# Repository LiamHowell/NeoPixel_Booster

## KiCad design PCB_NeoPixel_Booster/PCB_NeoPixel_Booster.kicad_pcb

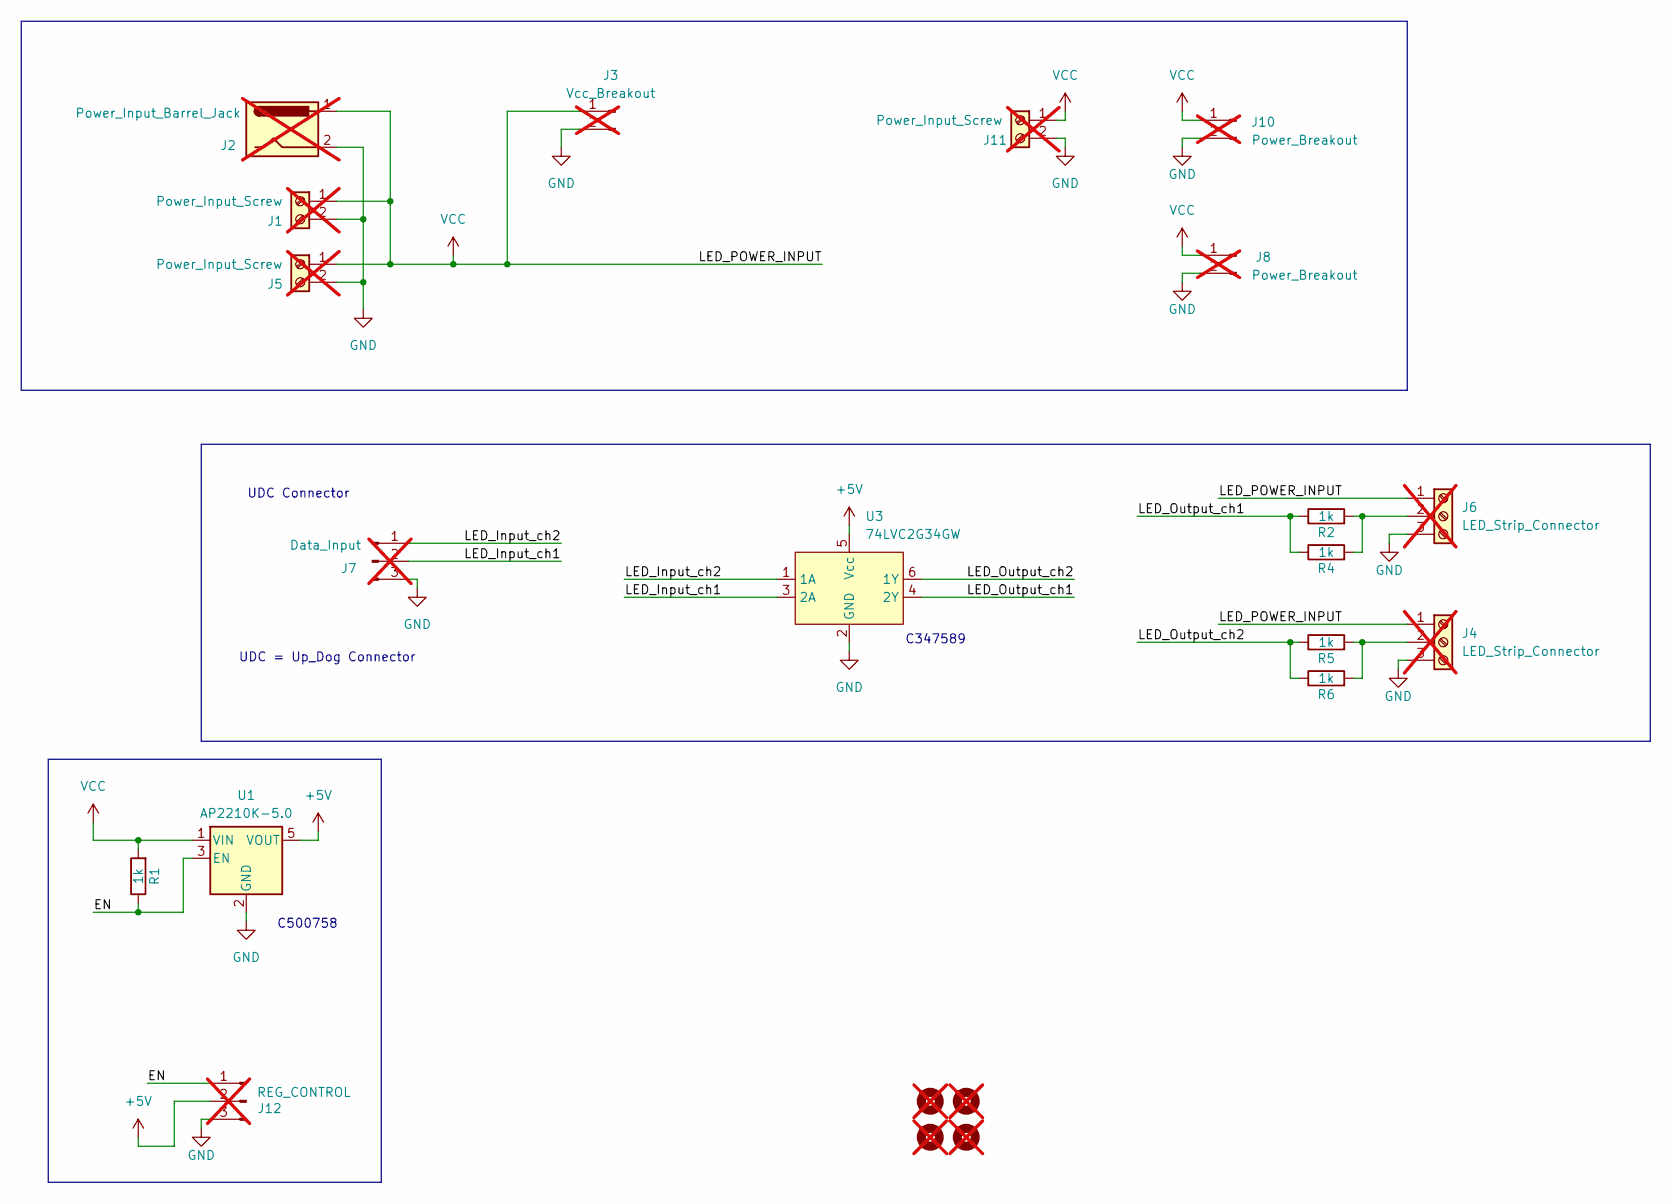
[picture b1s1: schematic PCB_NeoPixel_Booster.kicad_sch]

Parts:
H1, H2, H4, H5: MountingHole; MountingHole_4.3mm_M4; not fitted
J1, J5, J11: Power_Input_Screw; TerminalBlock_bornier-2_P5.08mm; not fitted
J2: Power_Input_Barrel_Jack; BarrelJack_Horizontal; not fitted
J3: Vcc_Breakout; PinHeader_1x02_P2.54mm_Vertical; not fitted
J4, J6: LED_Strip_Connector; TerminalBlock_Xinya_XY308-2.54-3P_1x03_P2.54mm_Horizontal; not fitted
J7: Data_Input; PinHeader_1x03_P2.54mm_Vertical; not fitted
J8, J10: Power_Breakout; PinHeader_1x02_P2.54mm_Vertical; not fitted
J12: REG_CONTROL; PinHeader_1x03_P2.54mm_Vertical; not fitted
R1, R2, R4, R5, R6: 1k; R_1206_3216Metric_Pad1.30x1.75mm_HandSolder; MPN C4410
U1: AP2210K-5.0; SOT-23-5; MPN C500758
U3: 74LVC2G34GW; SOT-23-6_Handsoldering; MPN C347589

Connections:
+5V: J12.2, U1.5 (VOUT), U3.5 (Vcc)
/EN: J12.1, R1.1, U1.3 (EN)
/LED_Input_ch1: J7.2, U3.3 (2A)
/LED_Input_ch2: J7.1, U3.1 (1A)
/LED_Output_ch1: R2.1, R4.1, U3.4 (2Y)
/LED_Output_ch2: R5.1, R6.1, U3.6 (1Y)
GND: J1.2, J2.2, J3.2, J4.3, J5.2, J6.3, J7.3, J8.2, J10.2, J11.2, J12.3, U1.2 (GND), U3.2 (GND)
unnamed: J4.2, R5.2, R6.2
unnamed: J6.2, R2.2, R4.2
VCC: J1.1, J2.1, J3.1, J4.1, J5.1, J6.1, J8.1, J10.1, J11.1, R1.2, U1.1 (VIN)

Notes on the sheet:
C500758
UDC Connector
UDC = Up_Dog Connector
C347589

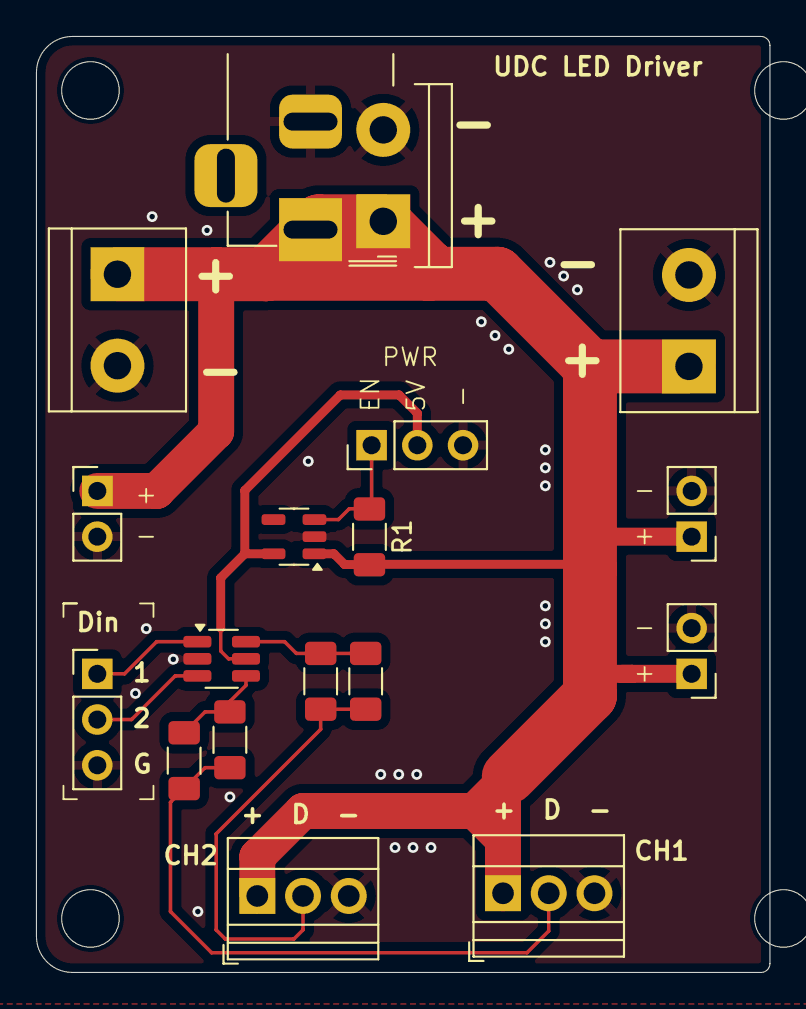
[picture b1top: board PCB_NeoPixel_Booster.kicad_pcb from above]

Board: 2 copper layers, 40.8 x 52.0 mm, 22 parts (0 on the bottom side), 10 nets.

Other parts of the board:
H1#2: MountingHole; MountingHole_3.2mm_M3

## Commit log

2026-01-04 Add Prod files
2026-01-06 Fin at last
